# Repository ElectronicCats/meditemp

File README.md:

# MediTemp

## ¿Qué es?
MediTemp-C es una estación autónoma de medición de temperatura corporal, ideal para la presente situación de contingencia nacional y mundial. 
Con MediTemp-C se puede realizar un control de acceso a establecimientos comerciales, bares, restaurantes, etc. 

La estación realiza una medición de temperatura corporal de manera no invasiva y sin contacto con las personas por medio de su sensor infrarrojo, además de realizar un conteo y registro de los datos los cuales pueden ser consultados y/o descargados vía inalámbrica por medio de cualquier dispositivo móvil o computadora

## ¿Cómo funciona?
1. La persona llega a la estación MediTemp-C acercando la frente o la parte interna de la muñeca al sensor de temperatura. La estación cuenta con un sensor de distancia indicando que tan cerca se debe de estar para una correcta medición.

2. Una vez realizada la medición de temperatura la estación muestra la temperatura de la persona por medio de una pantalla alfanumérica y guardará un registro el cual consiste en un conteo de personas, el valor medido de temperatura la fecha y la hora del registro. 

3. En caso de que se detecte a una persona con temperatura alta, la estación emitirá una alarma audible y encenderá un indicador luminoso. 

4. MediTemp-C cuenta con salidas electrónicas las cuales pueden activar o desactivar chapas o cerraduras magnéticas en caso de ser requerido para permitir o no permitir el acceso a personas con alta temperatura.

5. La estación muestra el conteo de personas que han ingresado en su pantalla y como aditamento adicional MediTemp-C cuenta con un contador de personas de salida, con lo cual se puede mostrar el número de personas que hay dentro del establecimiento

6. El registro de datos puede ser descargado vía inalámbrica por medio de cualquier teléfono móvil o computadora. también puede ser consultado vía internet desde cualquier parte del mundo. 

## Funcionalidades

Sensor de temperatura corporal 
Infrarrojo de no contacto
Pantalla alfanumérica para visualización de datos
Alarma audible Buzzer de 90dB 
Leds Indicadores grandes de 10mm brillantes 
Memoria SD para almacenamiento de datos
Conectividad WiFi 
2 salidas a relevador 
Tensión de contacto 220 VCD, 250 VAC. 
Corriente soportada 1A. 
Potencia 30W, 37.7 VA
Voltaje de trabajo 110 - 220 Vac 

## Caracteristicas Físicas

Estructura metálica a base de aluminio, medidas 20x20x5 cm. Lo cual proporciona alta duración y bajo peso (2kg). 
Puede ser Instalado en pared o con pedestal para piso con sujeción.
Compartimento para despachador de gel antibacterial.

## Aditamentos Adicionales

### Activación de cargas
MediTemp-C cuenta con dos salidas de relevador las cuales pueden ser usadas para la activación de puertas, chapas, cerraduras magnéticas, luminarias, u otros dispositivos. 

### Contador de personas de salida
La estación cuenta con la posibilidad de conectar un contador de personas de salida, el cual consiste en dos barras paralelas con sensores electrónicos compatible con la estación MediTemp-C. De esta forma, en la pantalla se mostrará el número de personas que hay en el momento en el  establecimiento.

# Licence

Electronic Cats invests time and resources providing this open source design, please support Electronic Cats and open-source hardware by purchasing products from Electronic Cats!

Designed by Electronic Cats.

Firmware released under an GNU AGPL v3.0 license. See the LICENSE file for more information.

Hardware released under an CERN Open Hardware Licence v1.2. See the LICENSE_HARDWARE file for more information.

Electronic Cats is a registered trademark, please do not use if you sell these PCBs.

November 2019

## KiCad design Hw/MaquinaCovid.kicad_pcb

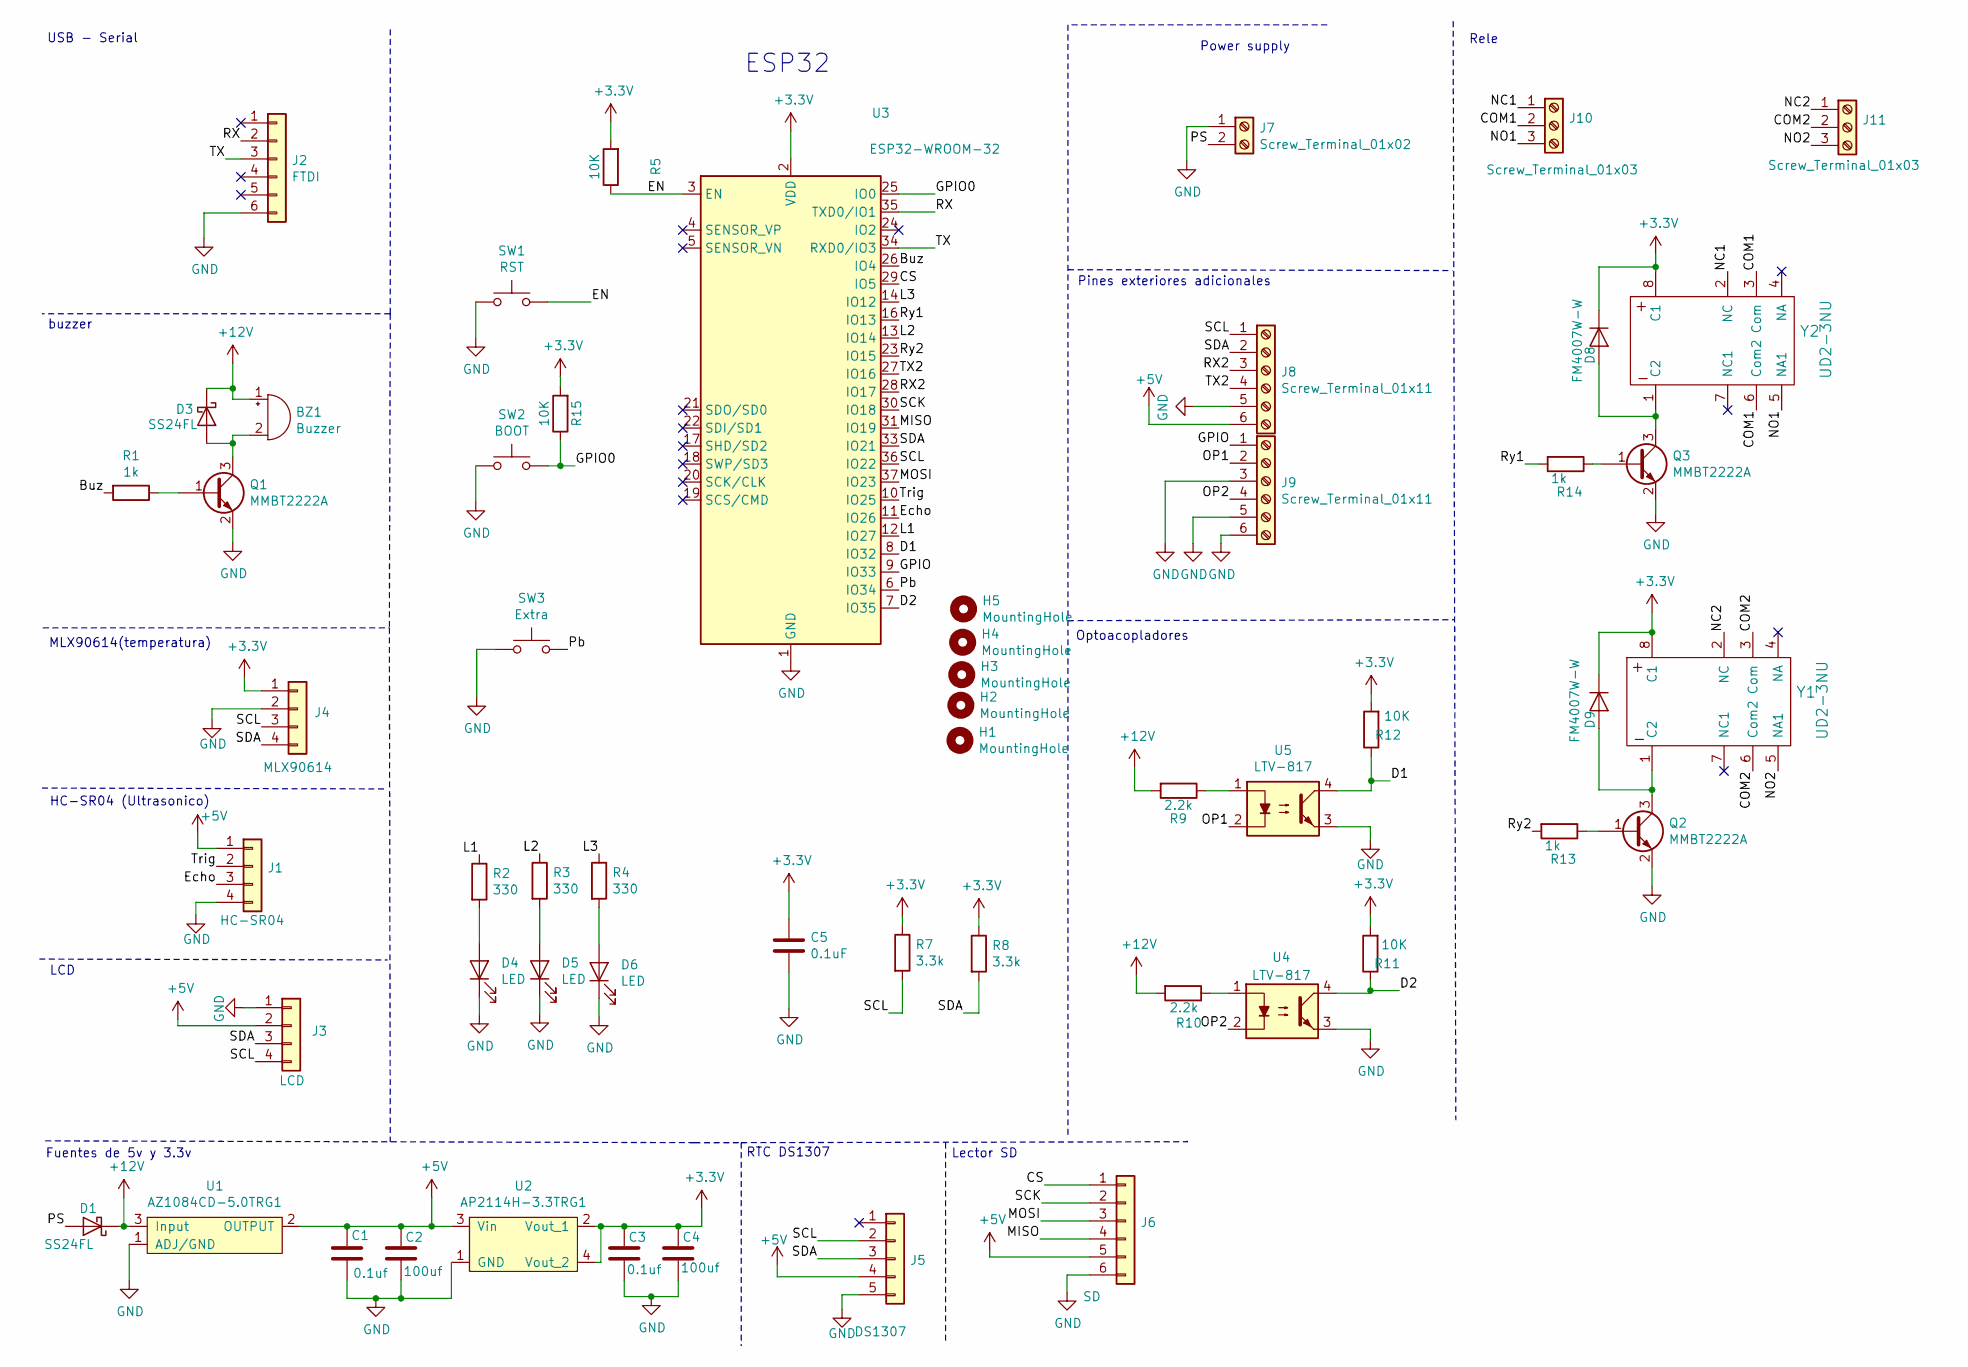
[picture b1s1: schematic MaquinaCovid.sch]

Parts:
BZ1: Buzzer
C1, C3: 0.1uf; C_0805_2012Metric_Pad1.15x1.40mm_HandSolder
C2, C4: 100uf; CP_EIA-3216-18_Kemet-A_Pad1.58x1.35mm_HandSolder
C5: 0.1uF; C_0805_2012Metric_Pad1.15x1.40mm_HandSolder
D1, D3: SS24FL; D_SOD-123F
D4, D5, D6: LED; PinHeader_1x02_P2.54mm_Vertical
D8, D9: FM4007W-W; F4007
H1, H2, H3, H4, H5: MountingHole; MountingHole_3.2mm_M3_Pad_Via
J1: HC-SR04; PinHeader_1x04_P2.54mm_Vertical
J2: FTDI; PinHeader_1x06_P2.54mm_Vertical
J3: LCD; PinHeader_1x04_P2.54mm_Vertical
J4: MLX90614; PinHeader_1x04_P2.54mm_Vertical
J5: DS1307; PinHeader_1x05_P2.54mm_Vertical
J6: SD; PinHeader_1x06_P2.54mm_Vertical
J7: Screw_Terminal_01x02; TerminalBlock_bornier-2_P5.08mm
J8, J9: Screw_Terminal_01x11; TerminalBlock_bornier-6_P5.08mm
J10, J11: Screw_Terminal_01x03; TerminalBlock_bornier-3_P5.08mm
Q1, Q2, Q3: MMBT2222A; SOT-23
R1, R13, R14: 1k; R_0805_2012Metric_Pad1.15x1.40mm_HandSolder
R2, R3, R4: 330; R_0805_2012Metric_Pad1.15x1.40mm_HandSolder
R5, R11, R12, R15: 10K; R_0805_2012Metric_Pad1.15x1.40mm_HandSolder
R7, R8: 3.3k; R_0805_2012Metric_Pad1.15x1.40mm_HandSolder
R9, R10: 2.2k; R_0805_2012Metric_Pad1.15x1.40mm_HandSolder
SW1: RST; SW_SPST_TL3342
SW2: BOOT; SW_SPST_TL3342
SW3: Extra; SW_SPST_TL3342
U1: AZ1084CD-5.0TRG1; TO-252-2
U2: AP2114H-3.3TRG1; SOT-223
U3: ESP32-WROOM-32
U4, U5: LTV-817; DIP-4_W7.62mm_Socket
Y1, Y2: UD2-3NU

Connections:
+3V3: C3.1, C4.1, C5.1, D8.1 (K), D9.1 (K), J4.1, R5.2, R7.1, R8.1, R11.2, R12.2, R15.2, U2.2 (Vout_1), U2.4 (Vout_2), U3.2 (VDD), Y1.8 (C1), Y2.8 (C1)
+5V: C1.1, C2.1, J1.1, J3.2, J5.4, J6.5, J8.6, U1.2 (OUTPUT), U2.3 (Vin)
+12V: BZ1.1 (-), D1.1 (K), D3.1 (K), R9.2, R10.2, U1.3 (Input)
/Buz: R1.2, U3.26 (IO4)
/COM1: J10.2, Y2.3 (Com), Y2.6 (Com2)
/COM2: J11.2, Y1.3 (Com), Y1.6 (Com2)
/CS: J6.1, U3.29 (IO5)
/D1: R12.1, U3.8 (IO32), U5.4
/D2: R11.1, U3.7 (IO35), U4.4
/EN: R5.1, SW1.2, U3.3 (EN)
/Echo: J1.3, U3.11 (IO26)
/GPIO: J9.1, U3.9 (IO33)
/GPIO0: R15.1, SW2.2, U3.25 (IO0)
/L1: R2.1, U3.12 (IO27)
/L2: R3.1, U3.13 (IO14)
/L3: R4.1, U3.14 (IO12)
/MISO: J6.4, U3.31 (IO19)
/MOSI: J6.3, U3.37 (IO23)
/NC1: J10.1, Y2.2 (NC)
/NC2: J11.1, Y1.2 (NC)
/NO1: J10.3, Y2.5 (NA1)
/NO2: J11.3, Y1.5 (NA1)
/OP1: J9.2, U5.2
/OP2: J9.4, U4.2
/PS: D1.2 (A), J7.2
/Pb: SW3.2, U3.6 (IO34)
/RX: J2.2, U3.35 (TXD0/IO1)
/RX2: J8.3, U3.28 (IO17)
/Ry1: R14.2, U3.16 (IO13)
/Ry2: R13.2, U3.23 (IO15)
/SCK: J6.2, U3.30 (IO18)
/SCL: J3.4, J4.3, J5.2, J8.1, R7.2, U3.36 (IO22)
/SDA: J3.3, J4.4, J5.3, J8.2, R8.2, U3.33 (IO21)
/TX: J2.3, U3.34 (RXD0/IO3)
/TX2: J8.4, U3.27 (IO16)
/Trig: J1.2, U3.10 (IO25)
GND: C1.2, C2.2, C3.2, C4.2, C5.2, D4.1 (K), D5.1 (K), D6.1 (K), J1.4, J2.6, J3.1, J4.2, J5.5, J6.6, J7.1, J8.5, J9.3, J9.5, J9.6, Q1.2 (E), Q2.2 (E), Q3.2 (E), SW1.1, SW2.1, SW3.1, U1.1 (ADJ/GND), U2.1 (GND), U3.1 (GND), U3.15 (GND), U3.38 (GND), U3.39 (GND), U4.3, U5.3
unnamed: BZ1.2 (+), D3.2 (A), Q1.3 (C)
unnamed: D4.2 (A), R2.2
unnamed: D5.2 (A), R3.2
unnamed: D6.2 (A), R4.2
unnamed: D8.2 (A), Q3.3 (C), Y2.1 (C2)
unnamed: D9.2 (A), Q2.3 (C), Y1.1 (C2)
unnamed: Q1.1 (B), R1.1
unnamed: Q2.1 (B), R13.1
unnamed: Q3.1 (B), R14.1
unnamed: R9.1, U5.1
unnamed: R10.1, U4.1

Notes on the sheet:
Fuentes de 5v y 3.3v
MLX90614(temperatura)
HC-SR04 (Ultrasonico)
LCD
buzzer
USB - Serial
ESP32
RTC DS1307
Lector SD
Power supply
Rele
Pines exteriores adicionales
Optoacopladores

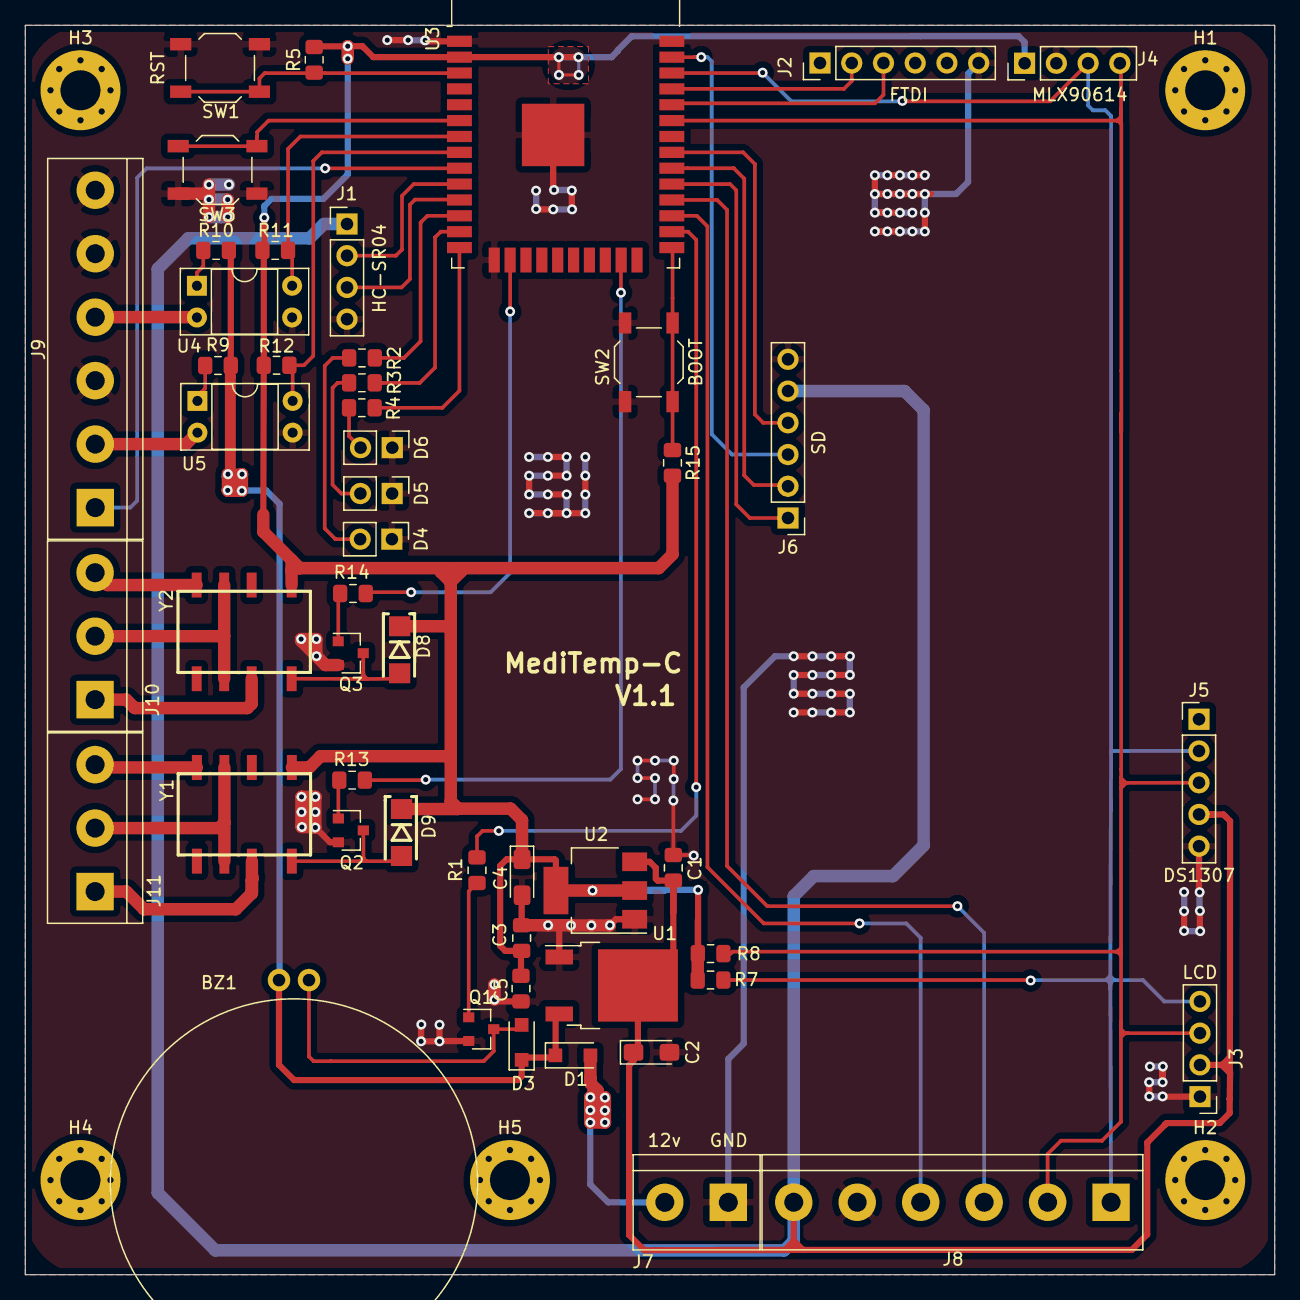
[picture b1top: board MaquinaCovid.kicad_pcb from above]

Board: 2 copper layers, 100.0 x 100.0 mm, 56 parts (0 on the bottom side), 48 nets.

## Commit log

2020-07-08 init firmware
2020-07-10 Add files via upload
    Schematic
2020-07-10 update description
2020-07-11 Finished schematic
2020-07-13 Schematic changes
2020-07-14 Added led
2020-07-15 Footprint placement (part 1)
2020-07-16 Finished PCB
2020-07-16 Add v1.0
2020-07-20 added sensor code
    I addded it on Hw to avoid conflicts with the firmware part
2020-07-21 add function temperature, lcd and others
2020-07-21 remove sketch
2020-07-23 Integration of the sensors on the program
2020-07-24 remove double serial and format
2020-08-05 More code
    SD and sensor code
2020-08-06 Added SD and RTC code
2020-08-06 format code
2020-08-06 Added wifimanager and OTA portal
2020-08-06 config OTA pin for extra button
2020-08-06 deleted delete
2020-08-06 Covid machine V1.1
    -Added pull-up to the boot button
    -Change of the conection of the buzzer and relay pines
    -Added 5v to the ultrasonic sensor
    -Removed the diode on FTDI's TX pin
    -Added missing names on the componens
